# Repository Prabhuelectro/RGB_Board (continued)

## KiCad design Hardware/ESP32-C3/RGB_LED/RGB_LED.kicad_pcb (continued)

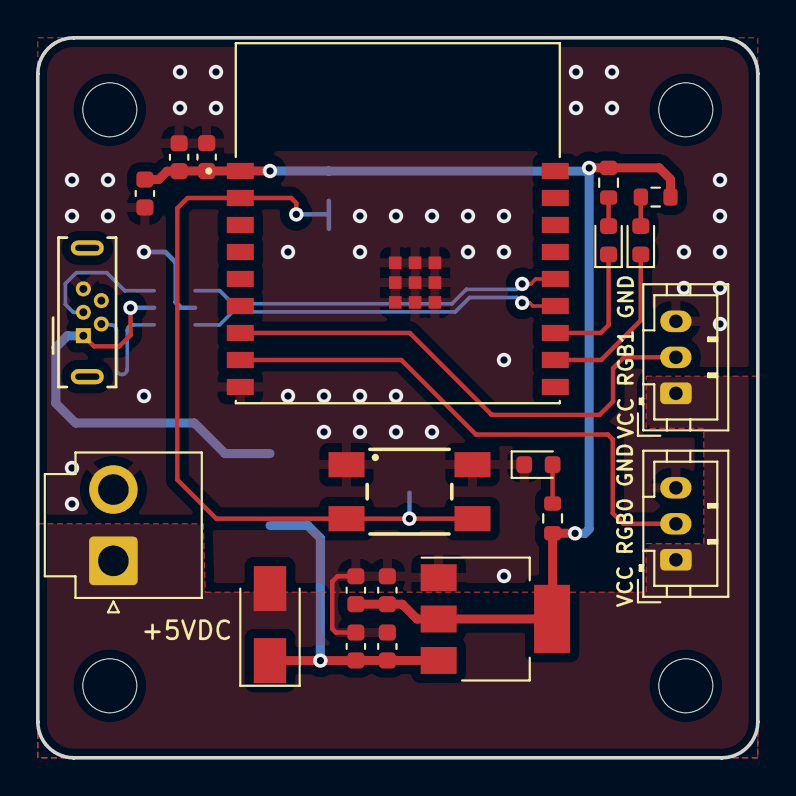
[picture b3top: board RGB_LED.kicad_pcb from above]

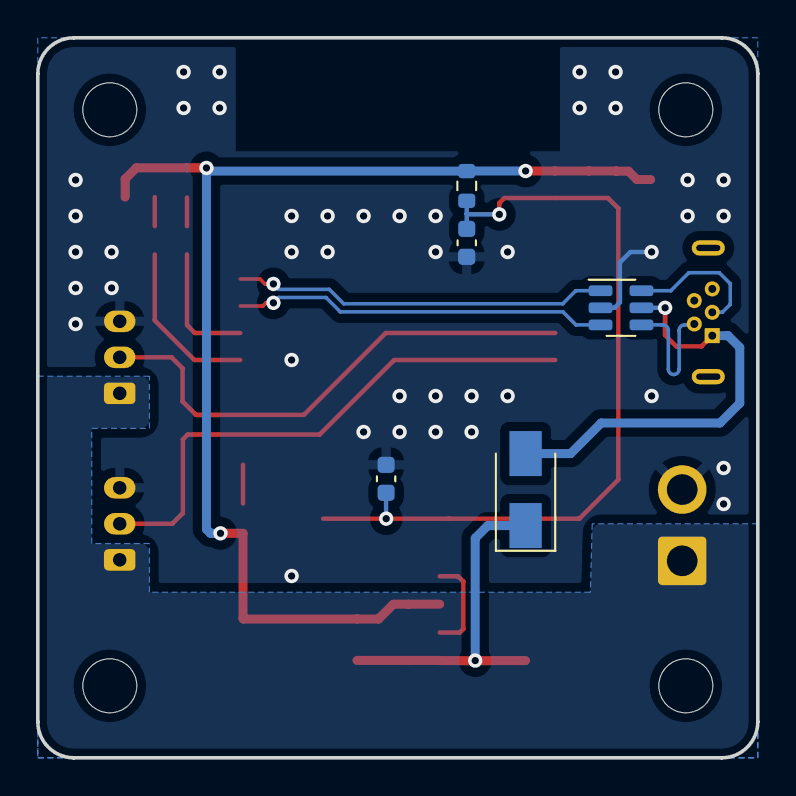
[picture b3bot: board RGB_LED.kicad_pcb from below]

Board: 2 copper layers, 40.0 x 40.0 mm, 30 parts (5 on the bottom side), 17 nets.

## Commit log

2023-10-10 RGB and Ultrasonic Boards
